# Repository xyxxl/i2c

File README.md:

i2c
===

stupid i2c peripherals

lcd - i2c interface to a lcd + 4 leds

keypad - i2c interface to a phone like keypad

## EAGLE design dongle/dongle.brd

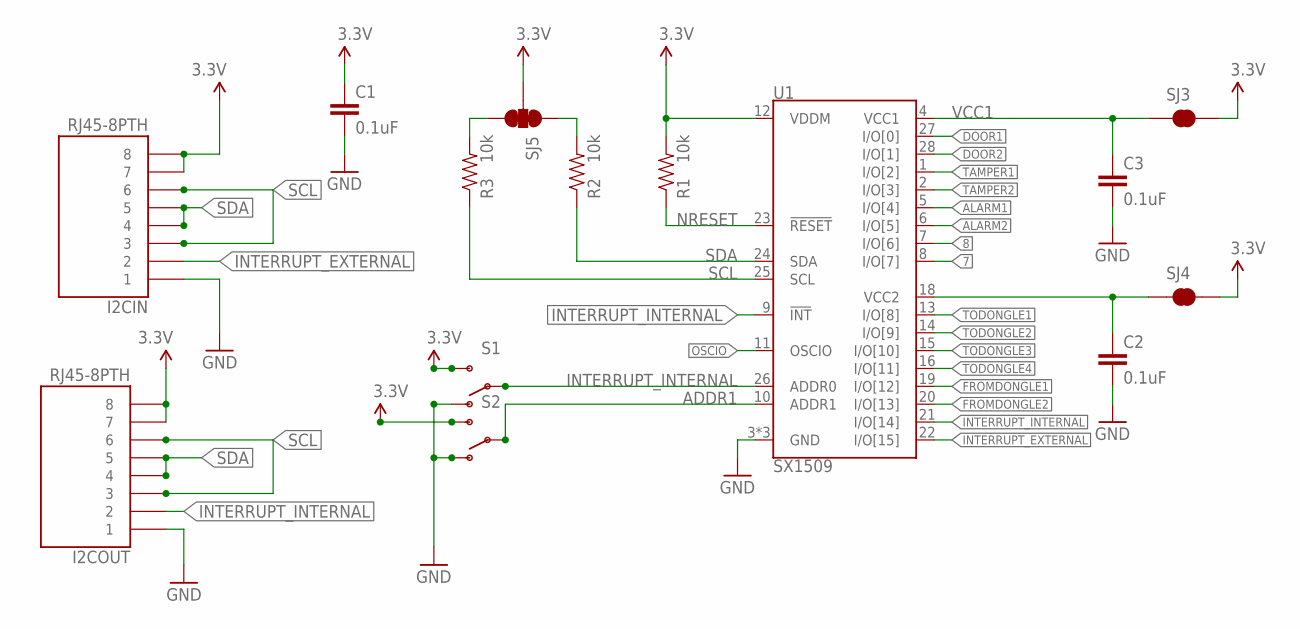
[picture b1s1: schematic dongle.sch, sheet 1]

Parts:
C1, C2, C3: 0.1uF; 0402-CAP
I2CIN, I2COUT: RJ45-8PTH; RJ45-8
R1, R2, R3: 10k; 0402-RES
S1, S2: SWITCH-SPDT-SMD-A; SWITCH-SPST-SMD-A
SJ3, SJ4: SOLDERJUMPERNO; SJ_2S-NO
SJ5: SOLDERJUMPER_2WAYS; SJ_3
U1: SX1509; QFN-28

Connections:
3.3V: C1.1, I2CIN.7, I2CIN.8, I2COUT.7, I2COUT.8, R1.2, S1.3 (S), S2.3 (S), SJ3.2, SJ4.2, SJ5.2, U1.12 (VDDM); also elsewhere on the board
7: U1.8 (I/O[7])
8: U1.7 (I/O[6])
ADDR1: S2.2, U1.10 (ADDR1)
ALARM1: U1.5 (I/O[4]); also elsewhere on the board
ALARM2: U1.6 (I/O[5]); also elsewhere on the board
DOOR1: U1.27 (I/O[0]); also elsewhere on the board
DOOR2: U1.28 (I/O[1]); also elsewhere on the board
FROMDONGLE1: U1.19 (I/O[12]); also elsewhere on the board
FROMDONGLE2: U1.20 (I/O[13]); also elsewhere on the board
GND: C1.2, C2.2, C3.2, I2CIN.1, I2COUT.1, S1.1 (O), S2.1 (O), U1.3 (GND), U1.17 (GND), U1.29 (GND); also elsewhere on the board
INTERRUPT_EXTERNAL: I2CIN.2, U1.22 (I/O[15])
INTERRUPT_INTERNAL: I2COUT.2, S1.2, U1.9 (!INT), U1.21 (I/O[14]), U1.26 (ADDR0)
unnamed: R3.2, SJ5.3
unnamed: R2.2, SJ5.1
NRESET: R1.1, U1.23 (!RESET)
OSCIO: U1.11 (OSCIO)
SCL: I2CIN.3, I2CIN.6, I2COUT.3, I2COUT.6, R3.1, U1.25 (SCL)
SDA: I2CIN.4, I2CIN.5, I2COUT.4, I2COUT.5, R2.1, U1.24 (SDA)
TAMPER1: U1.1 (I/O[2]); also elsewhere on the board
TAMPER2: U1.2 (I/O[3]); also elsewhere on the board
TODONGLE1: U1.13 (I/O[8]); also elsewhere on the board
TODONGLE2: U1.14 (I/O[9]); also elsewhere on the board
TODONGLE3: U1.15 (I/O[10]); also elsewhere on the board
TODONGLE4: U1.16 (I/O[11]); also elsewhere on the board
VCC1: C3.1, SJ3.1, U1.4 (VCC1)
VCC2: C2.1, SJ4.1, U1.18 (VCC2)

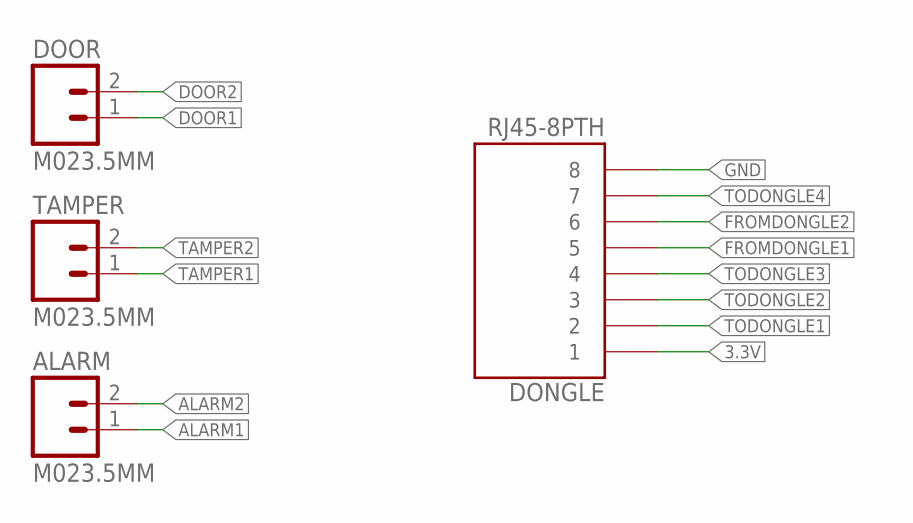
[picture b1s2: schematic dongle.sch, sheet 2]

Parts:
ALARM: M023.5MM; SCREWTERMINAL-3.5MM-2
DONGLE: RJ45-8PTH; RJ45-8
DOOR: M023.5MM; SCREWTERMINAL-3.5MM-2
TAMPER: M023.5MM; SCREWTERMINAL-3.5MM-2

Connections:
3.3V: DONGLE.1; also elsewhere on the board
ALARM1: ALARM.1; also elsewhere on the board
ALARM2: ALARM.2; also elsewhere on the board
DOOR1: DOOR.1; also elsewhere on the board
DOOR2: DOOR.2; also elsewhere on the board
FROMDONGLE1: DONGLE.5; also elsewhere on the board
FROMDONGLE2: DONGLE.6; also elsewhere on the board
GND: DONGLE.8; also elsewhere on the board
TAMPER1: TAMPER.1; also elsewhere on the board
TAMPER2: TAMPER.2; also elsewhere on the board
TODONGLE1: DONGLE.2; also elsewhere on the board
TODONGLE2: DONGLE.3; also elsewhere on the board
TODONGLE3: DONGLE.4; also elsewhere on the board
TODONGLE4: DONGLE.7; also elsewhere on the board

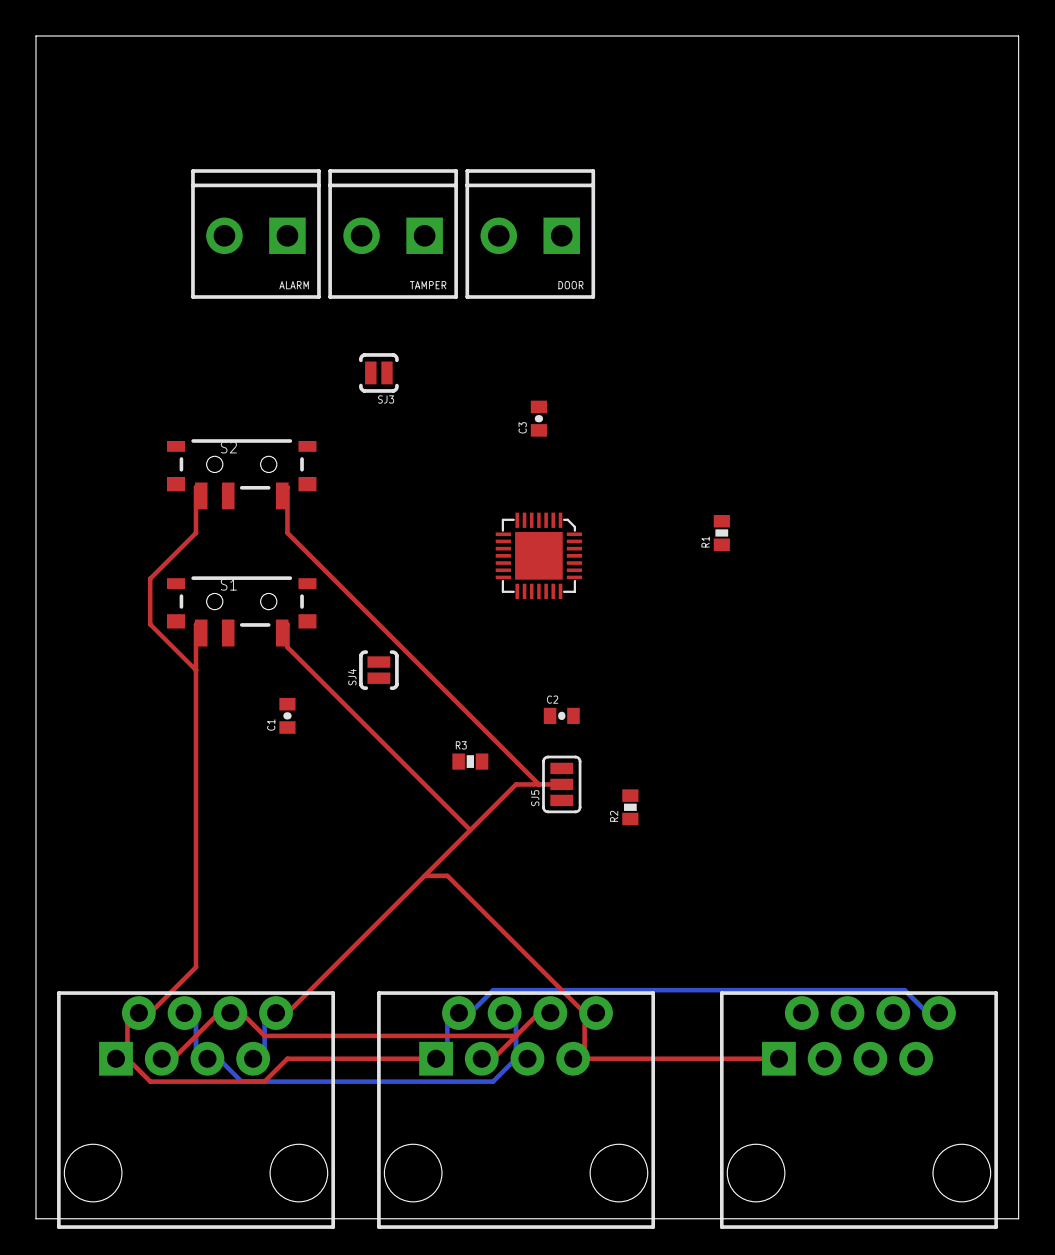
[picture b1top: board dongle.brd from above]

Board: 2 copper layers, 54.6 x 65.7 mm, 18 parts (0 on the bottom side), 24 nets.

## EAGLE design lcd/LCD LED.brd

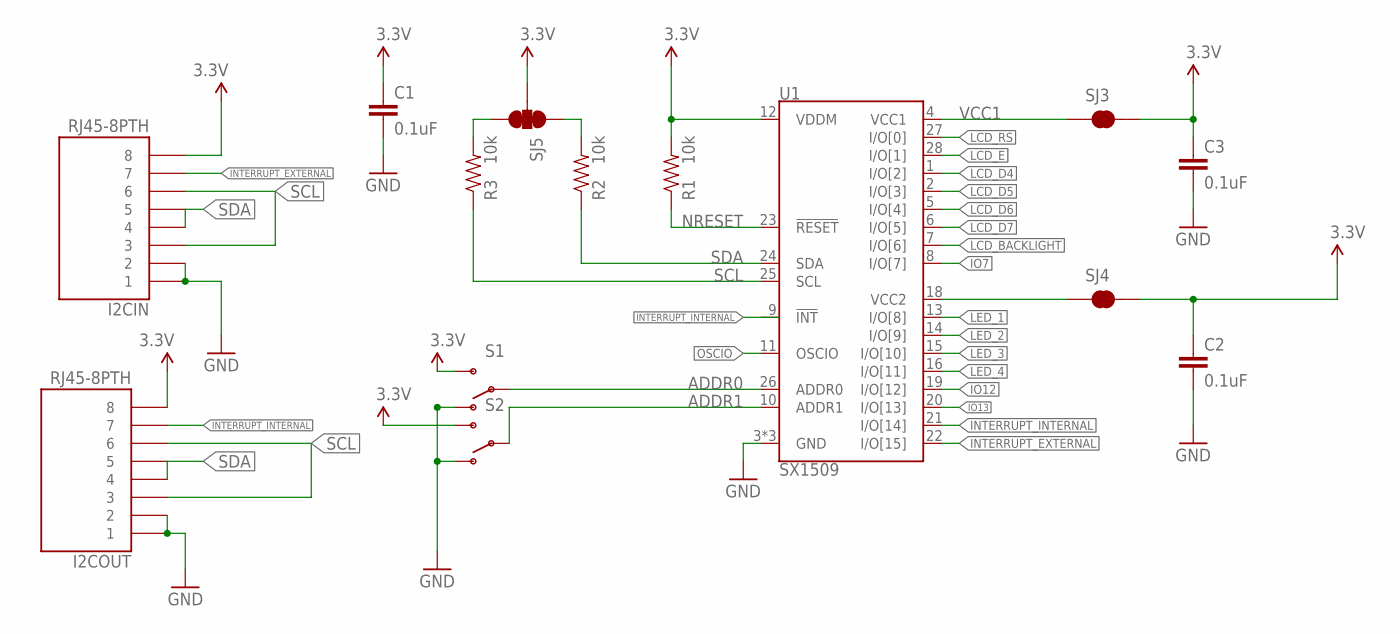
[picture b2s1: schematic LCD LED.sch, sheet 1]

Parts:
C1, C2, C3: 0.1uF; 0402-CAP
I2CIN, I2COUT: RJ45-8PTH; RJ45-8
R1, R2, R3: 10k; 0402-RES
S1, S2: SWITCH-SPDT-SMD-A; SWITCH-SPST-SMD-A
SJ3, SJ4: SOLDERJUMPERNO; SJ_2S-NO
SJ5: SOLDERJUMPER_2WAYS; SJ_3
U1: SX1509; QFN-28

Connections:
3.3V: C1.1, C2.1, C3.1, I2CIN.8, I2COUT.8, R1.2, S1.3 (S), S2.3 (S), SJ3.2, SJ4.2, SJ5.2, U1.12 (VDDM); also elsewhere on the board
ADDR0: S1.2, U1.26 (ADDR0)
ADDR1: S2.2, U1.10 (ADDR1)
GND: C1.2, C2.2, C3.2, I2CIN.1, I2CIN.2, I2COUT.1, I2COUT.2, S1.1 (O), S2.1 (O), U1.3 (GND), U1.17 (GND), U1.29 (GND); also elsewhere on the board
IO7: U1.8 (I/O[7])
LCD_BACKLIGHT: U1.7 (I/O[6]); also elsewhere on the board
LCD_D4: U1.1 (I/O[2]); also elsewhere on the board
LCD_D5: U1.2 (I/O[3]); also elsewhere on the board
LCD_D6: U1.5 (I/O[4]); also elsewhere on the board
LCD_D7: U1.6 (I/O[5]); also elsewhere on the board
LCD_E: U1.28 (I/O[1]); also elsewhere on the board
LCD_RS: U1.27 (I/O[0]); also elsewhere on the board
LED_1: U1.13 (I/O[8]); also elsewhere on the board
LED_2: U1.14 (I/O[9]); also elsewhere on the board
LED_3: U1.15 (I/O[10]); also elsewhere on the board
LED_4: U1.16 (I/O[11]); also elsewhere on the board
unnamed: R3.2, SJ5.3
unnamed: R2.2, SJ5.1
NRESET: R1.1, U1.23 (!RESET)
OSCIO: U1.11 (OSCIO)
SCL: I2CIN.3, I2CIN.6, I2COUT.3, I2COUT.6, R3.1, U1.25 (SCL)
SDA: I2CIN.4, I2CIN.5, I2COUT.4, I2COUT.5, R2.1, U1.24 (SDA)
VCC1: SJ3.1, U1.4 (VCC1)
VCC2: SJ4.1, U1.18 (VCC2)

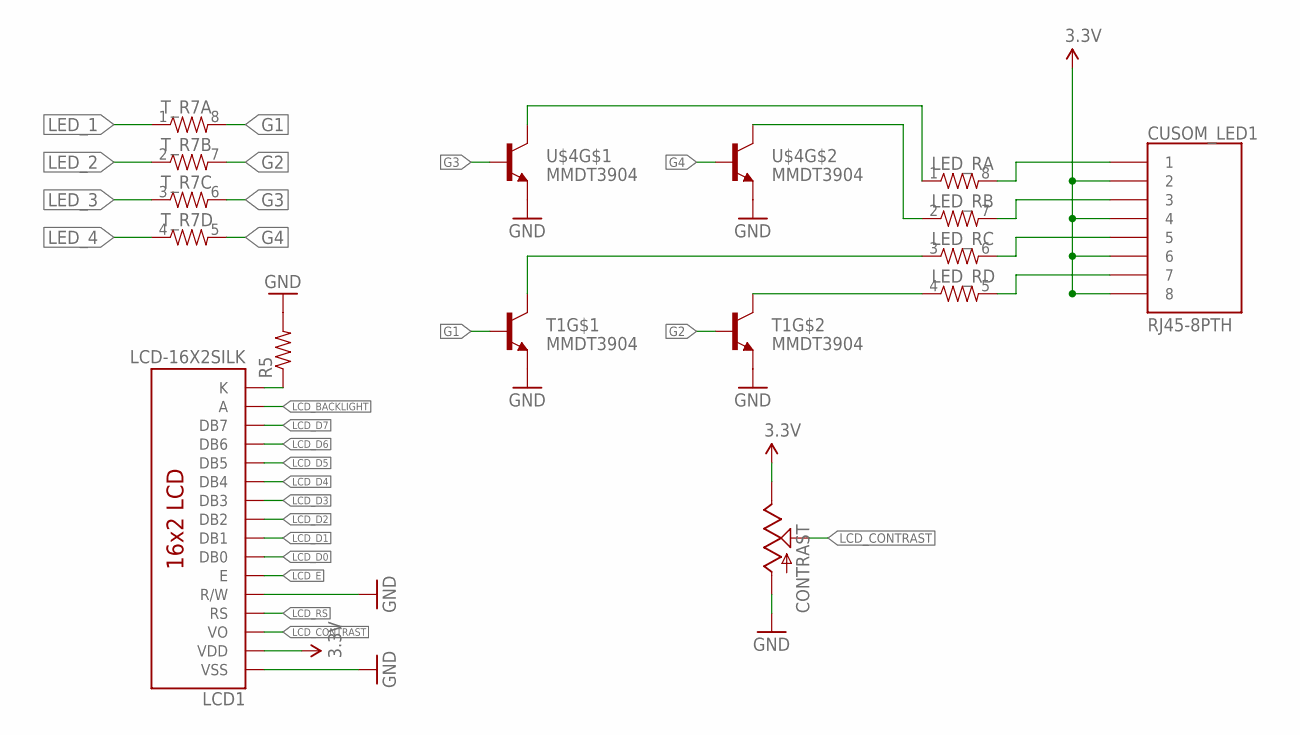
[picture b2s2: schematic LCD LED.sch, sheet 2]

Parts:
CONTRAST: POT; ALPS_POT
CUSOM_LED1: RJ45-8PTH; RJ45-8
LCD1: LCD-16X2SILK; LCD-16X2
LED_R: RESISTOR-ARRAY0603-ARV; 0603-ARV
R5: RESISTOR0603; 0603-RES
T1: MMDT3904; SOT363
T_R7: RESISTOR-ARRAY0603-ARV; 0603-ARV
U$4: MMDT3904; SOT363

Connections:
3.3V: CONTRAST.P$1 (E), CUSOM_LED1.2, CUSOM_LED1.4, CUSOM_LED1.6, CUSOM_LED1.8, LCD1.2 (VDD); also elsewhere on the board
G1: T1.5 (B), T_R7.8 (2)
G2: T1.2 (B), T_R7.7 (2)
G3: T_R7.6 (2), U$4.5 (B)
G4: T_R7.5 (2), U$4.2 (B)
GND: CONTRAST.P$3 (A), LCD1.1 (VSS), LCD1.5 (R/W), R5.2, T1.1 (E), T1.4 (E), U$4.1 (E), U$4.4 (E); also elsewhere on the board
LCD_BACKLIGHT: LCD1.15 (A); also elsewhere on the board
LCD_CONTRAST: CONTRAST.P$2 (S), LCD1.3 (VO)
LCD_D0: LCD1.7 (DB0)
LCD_D1: LCD1.8 (DB1)
LCD_D2: LCD1.9 (DB2)
LCD_D3: LCD1.10 (DB3)
LCD_D4: LCD1.11 (DB4); also elsewhere on the board
LCD_D5: LCD1.12 (DB5); also elsewhere on the board
LCD_D6: LCD1.13 (DB6); also elsewhere on the board
LCD_D7: LCD1.14 (DB7); also elsewhere on the board
LCD_E: LCD1.6 (E); also elsewhere on the board
LCD_RS: LCD1.4 (RS); also elsewhere on the board
LED_1: T_R7.1; also elsewhere on the board
LED_2: T_R7.2 (1); also elsewhere on the board
LED_3: T_R7.3 (1); also elsewhere on the board
LED_4: T_R7.4 (1); also elsewhere on the board
unnamed: CUSOM_LED1.1, LED_R.8 (2)
unnamed: LCD1.16 (K), R5.1
unnamed: CUSOM_LED1.3, LED_R.7 (2)
unnamed: CUSOM_LED1.5, LED_R.6 (2)
unnamed: CUSOM_LED1.7, LED_R.5 (2)
unnamed: LED_R.1, U$4.3 (C)
unnamed: LED_R.2 (1), U$4.6 (C)
unnamed: LED_R.3 (1), T1.3 (C)
unnamed: LED_R.4 (1), T1.6 (C)

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
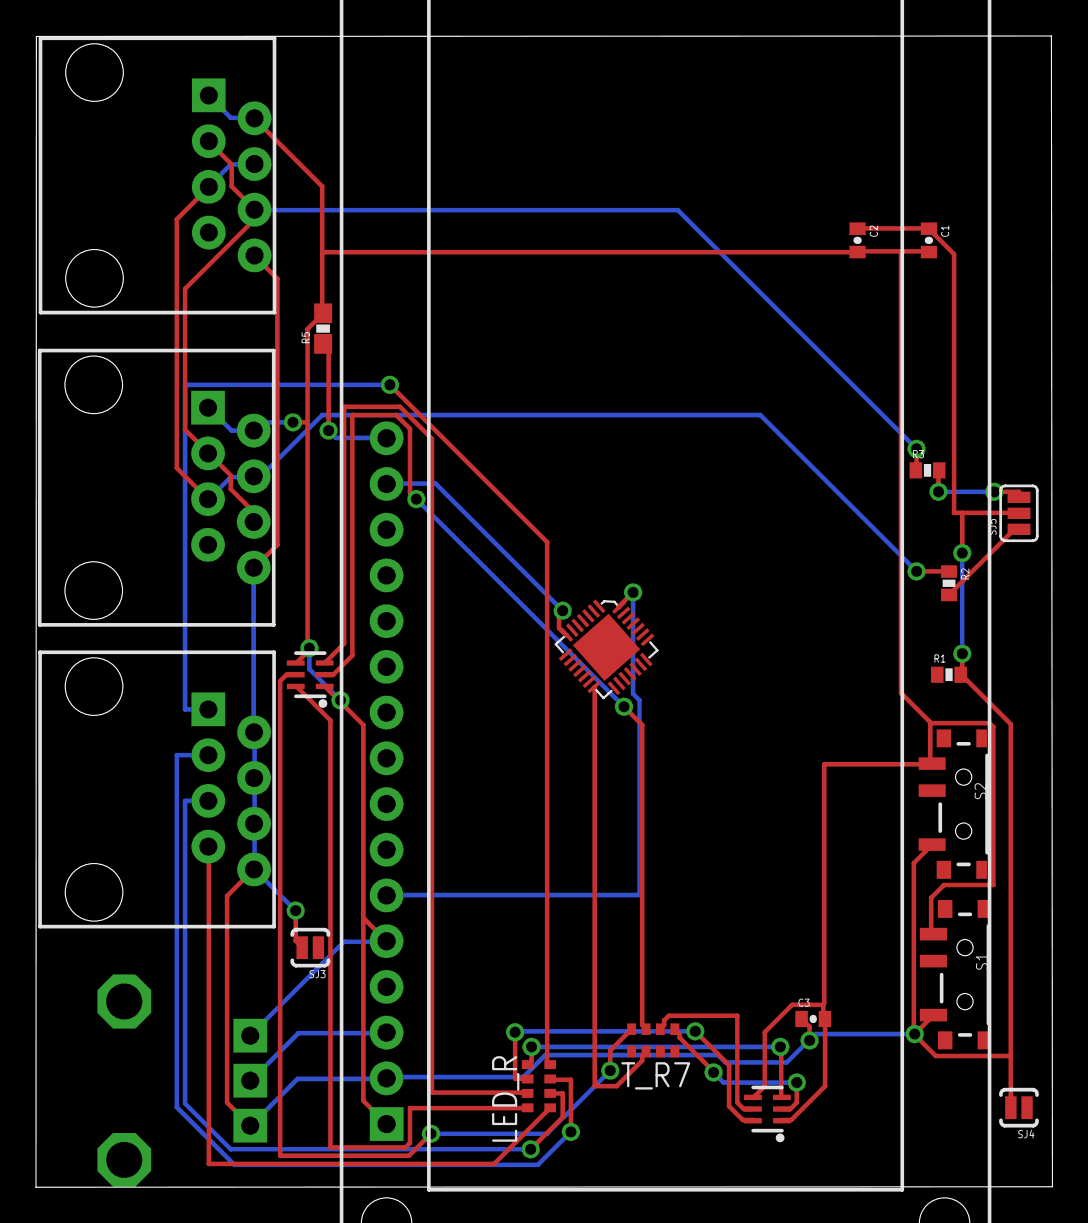
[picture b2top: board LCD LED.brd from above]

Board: 2 copper layers, 56.5 x 64.0 mm, 22 parts (0 on the bottom side), 38 nets.

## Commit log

2014-04-29 initial designs for i2c stuff
2014-04-29 added in the pdf for the sx1509 chip used in the design
2014-04-29 added datasheet for a keypad
2014-06-27 added in changes to the lcd to use 4 wire interface updated other schematics to have cascading of interrupt
2014-06-27 adding in schematic updates and some code..

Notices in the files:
parts and their libraries:
SparkFun-DigitalIC: Licensing: CC v3.0 Share-Alike You are welcome to use this library for commercial purposes.
SparkFun-Electromechanical: Licensing: Creative Commons ShareAlike 4.0 International - https://creativecommons.org/licenses/by-sa/4.0
